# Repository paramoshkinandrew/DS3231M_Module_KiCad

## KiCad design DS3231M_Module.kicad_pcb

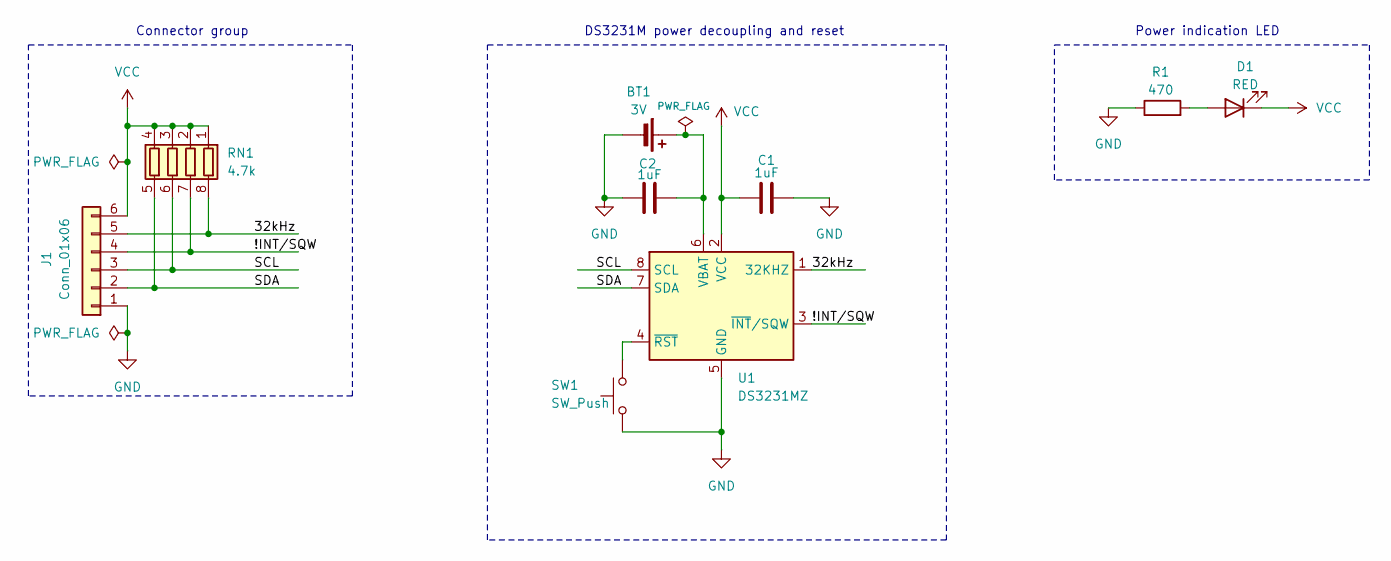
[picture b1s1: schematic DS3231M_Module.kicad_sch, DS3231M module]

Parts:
BT1: 3V; Battery_Panasonic_CR2032-HFN_Horizontal_CircularHoles
C1, C2: 1uF; C_0201_0603Metric_Pad0.64x0.40mm_HandSolder
D1: RED; LED_0201_0603Metric_Pad0.64x0.40mm_HandSolder
J1: Conn_01x06; PinHeader_1x06_P2.54mm_Vertical
R1: 470; R_0402_1005Metric_Pad0.72x0.64mm_HandSolder
RN1: 4.7k; R_Array_Convex_4x0603
SW1: SW_Push; SW_SPST_PTS810
U1: DS3231MZ; SOIC-8_3.9x4.9mm_P1.27mm

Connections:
/32kHz: J1.5, RN1.8 (R1.2), U1.1 (32KHZ)
/!INT/SQW: J1.4, RN1.7 (R2.2), U1.3 (~INT/SQW)
/SCL: J1.3, RN1.6 (R3.2), U1.8 (SCL)
/SDA: J1.2, RN1.5 (R4.2), U1.7 (SDA)
GND: BT1.2 (-), C1.2, C2.1, J1.1, R1.1, SW1.1, U1.5 (GND)
unnamed: BT1.1 (+), C2.2, U1.6 (VBAT)
unnamed: D1.2 (A), R1.2
unnamed: SW1.2, U1.4 (~RST)
VCC: C1.1, D1.1 (K), J1.6, RN1.1 (R1.1), RN1.2 (R2.1), RN1.3 (R3.1), RN1.4 (R4.1), U1.2 (VCC)

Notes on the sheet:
Connector group
DS3231M power decoupling and reset
Power indication LED

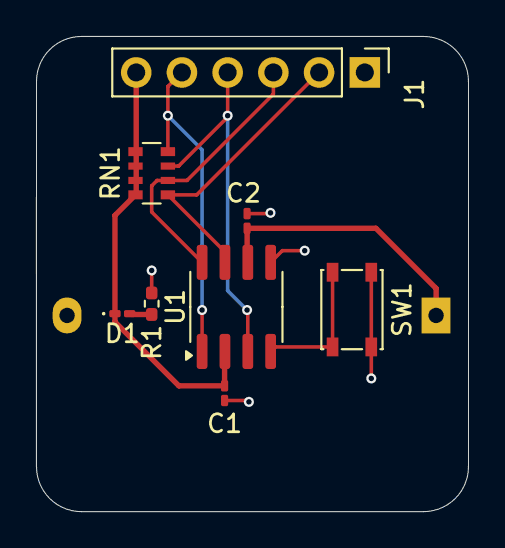
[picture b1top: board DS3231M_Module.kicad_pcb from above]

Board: 2 copper layers, 24.0 x 26.4 mm, 9 parts (1 on the bottom side), 9 nets.

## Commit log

2024-07-04 Add license
